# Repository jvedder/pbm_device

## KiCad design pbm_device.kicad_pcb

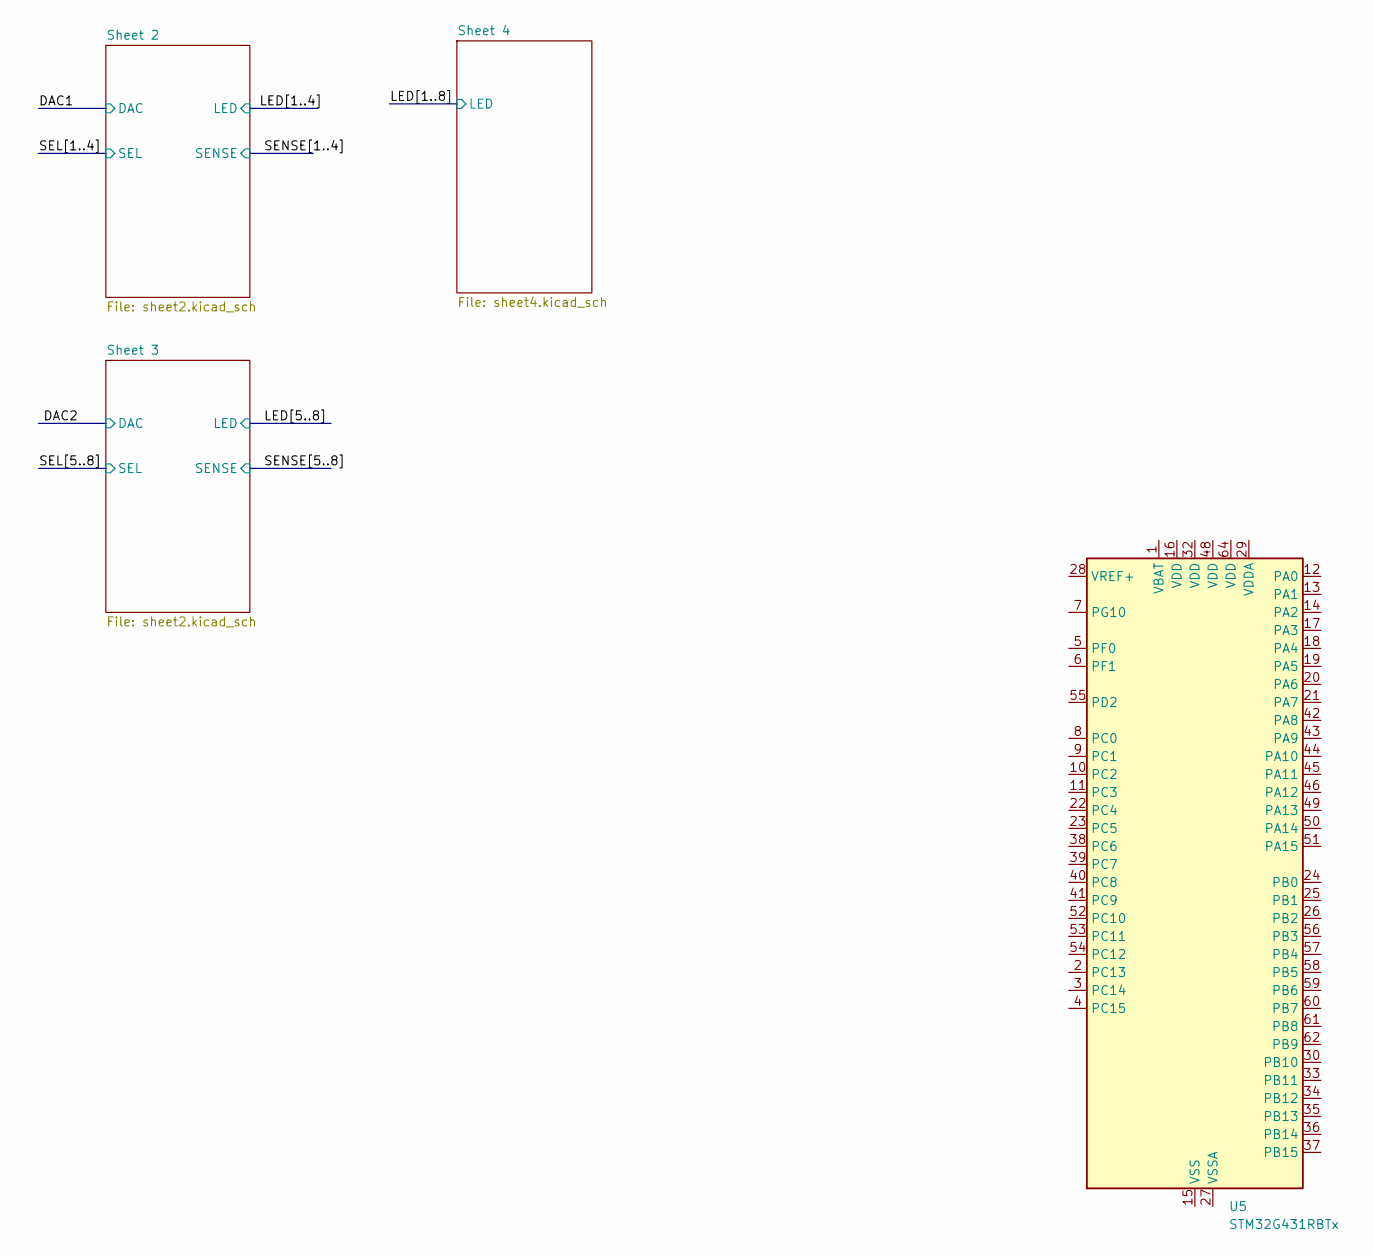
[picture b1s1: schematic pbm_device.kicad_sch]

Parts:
U5: STM32G431RBTx; LQFP-64_10x10mm_P0.5mm

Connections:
unnamed: U5.15 (VSS), U5.31 (VSS), U5.47 (VSS), U5.63 (VSS)

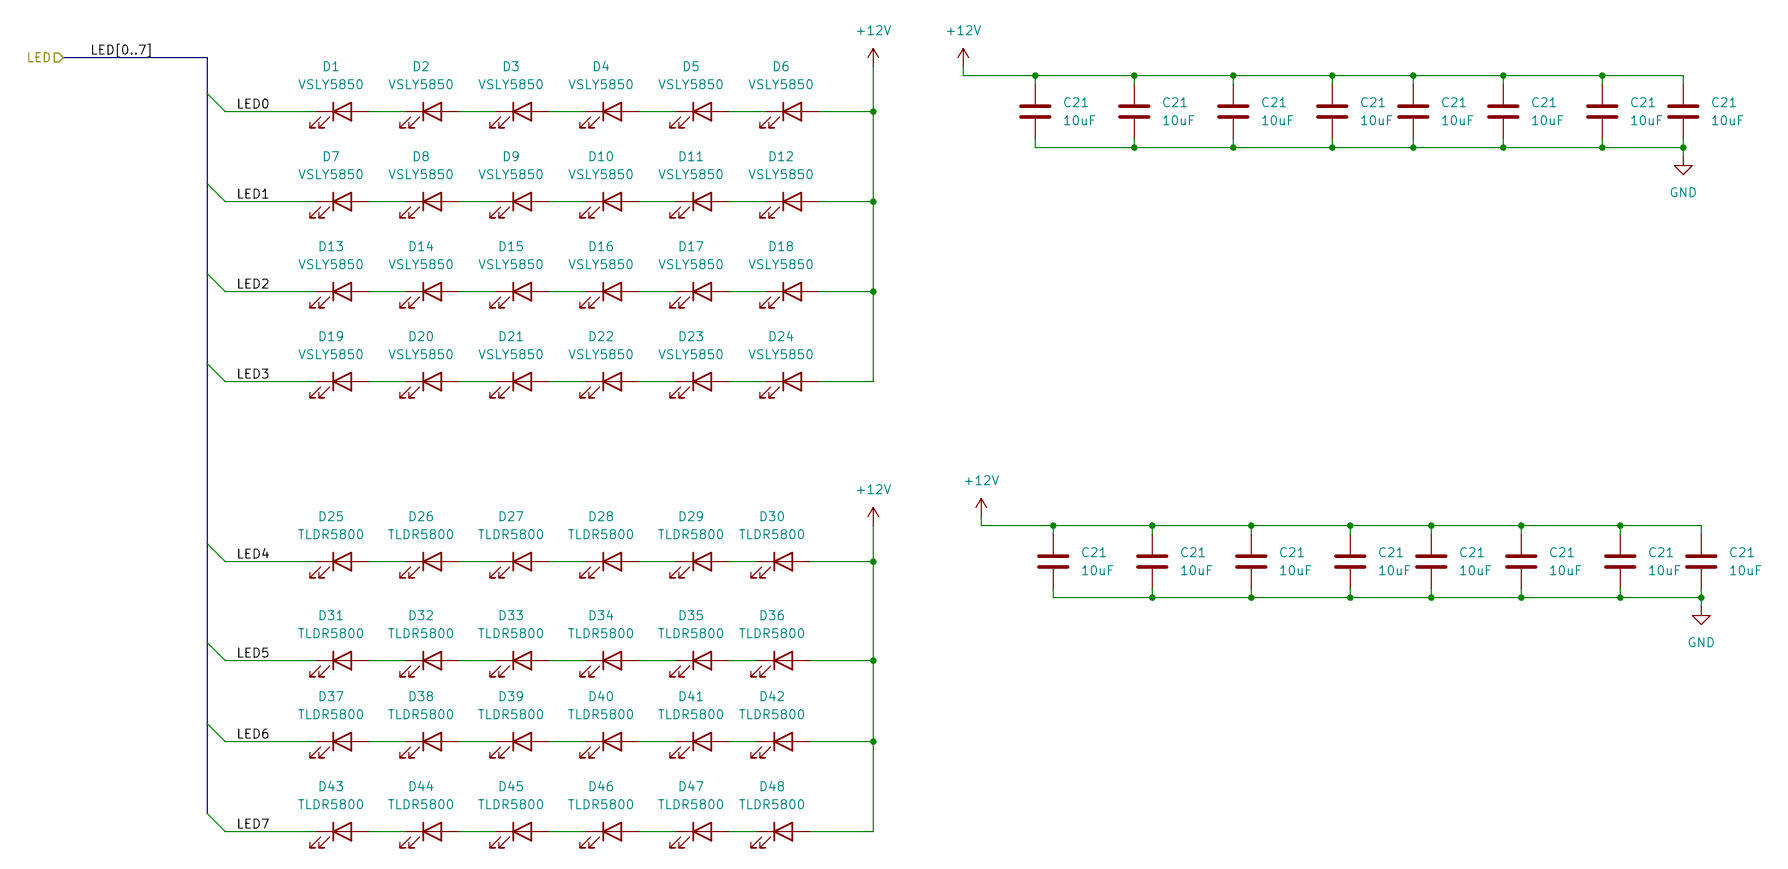
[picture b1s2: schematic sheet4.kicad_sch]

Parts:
C21: 10uF; R_0603_1608Metric_Pad0.98x0.95mm_HandSolder
D1, D2, D3, D4, D5, D6, D7, D8, D9, D10, D11, D12, D13, D14, D15, D16, D17, D18, D19, D20, D21, D22, D23, D24: VSLY5850; LED_D5.0mm
D25, D26, D27, D28, D29, D30, D31, D32, D33, D34, D35, D36, D37, D38, D39, D40, D41, D42, D43, D44, D45, D46, D47, D48: TLDR5800; LED_D5.0mm

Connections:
/LED1: D1.1 (K); also elsewhere on the board
/LED2: D7.1 (K); also elsewhere on the board
/LED3: D13.1 (K); also elsewhere on the board
/LED4: D19.1 (K); also elsewhere on the board
/LED5: D25.1 (K); also elsewhere on the board
/LED6: D31.1 (K); also elsewhere on the board
/LED7: D37.1 (K); also elsewhere on the board
/LED8: D43.1 (K); also elsewhere on the board
GND: C21.2; also elsewhere on the board
unnamed: D1.2 (A), D2.1 (K)
unnamed: D2.2 (A), D3.1 (K)
unnamed: D3.2 (A), D4.1 (K)
unnamed: D4.2 (A), D5.1 (K)
unnamed: D5.2 (A), D6.1 (K)
unnamed: D7.2 (A), D8.1 (K)
unnamed: D8.2 (A), D9.1 (K)
unnamed: D10.2 (A), D11.1 (K)
unnamed: D9.2 (A), D10.1 (K)
unnamed: D11.2 (A), D12.1 (K)
unnamed: D13.2 (A), D14.1 (K)
unnamed: D14.2 (A), D15.1 (K)
unnamed: D15.2 (A), D16.1 (K)
unnamed: D16.2 (A), D17.1 (K)
unnamed: D17.2 (A), D18.1 (K)
unnamed: D19.2 (A), D20.1 (K)
unnamed: D20.2 (A), D21.1 (K)
unnamed: D21.2 (A), D22.1 (K)
unnamed: D22.2 (A), D23.1 (K)
unnamed: D23.2 (A), D24.1 (K)
unnamed: D25.2 (A), D26.1 (K)
unnamed: D26.2 (A), D27.1 (K)
unnamed: D27.2 (A), D28.1 (K)
unnamed: D28.2 (A), D29.1 (K)
unnamed: D29.2 (A), D30.1 (K)
unnamed: D31.2 (A), D32.1 (K)
unnamed: D32.2 (A), D33.1 (K)
unnamed: D33.2 (A), D34.1 (K)
unnamed: D34.2 (A), D35.1 (K)
unnamed: D35.2 (A), D36.1 (K)
unnamed: D37.2 (A), D38.1 (K)
unnamed: D38.2 (A), D39.1 (K)
unnamed: D39.2 (A), D40.1 (K)
unnamed: D40.2 (A), D41.1 (K)
unnamed: D41.2 (A), D42.1 (K)
unnamed: D43.2 (A), D44.1 (K)
unnamed: D44.2 (A), D45.1 (K)
unnamed: D45.2 (A), D46.1 (K)
unnamed: D46.2 (A), D47.1 (K)
unnamed: D47.2 (A), D48.1 (K)

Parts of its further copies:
C5, C6, C7, C8, C9, C12, C13, C14, C15, C16, C17, C18, C19, C20, C22: 10uF; R_0603_1608Metric_Pad0.98x0.95mm_HandSolder

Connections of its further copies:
GND: C5.2, C6.2, C7.2, C8.2, C9.2, C12.2, C13.2, C14.2, C15.2, C16.2, C17.2, C18.2, C19.2, C20.2, C22.2; also elsewhere on the board

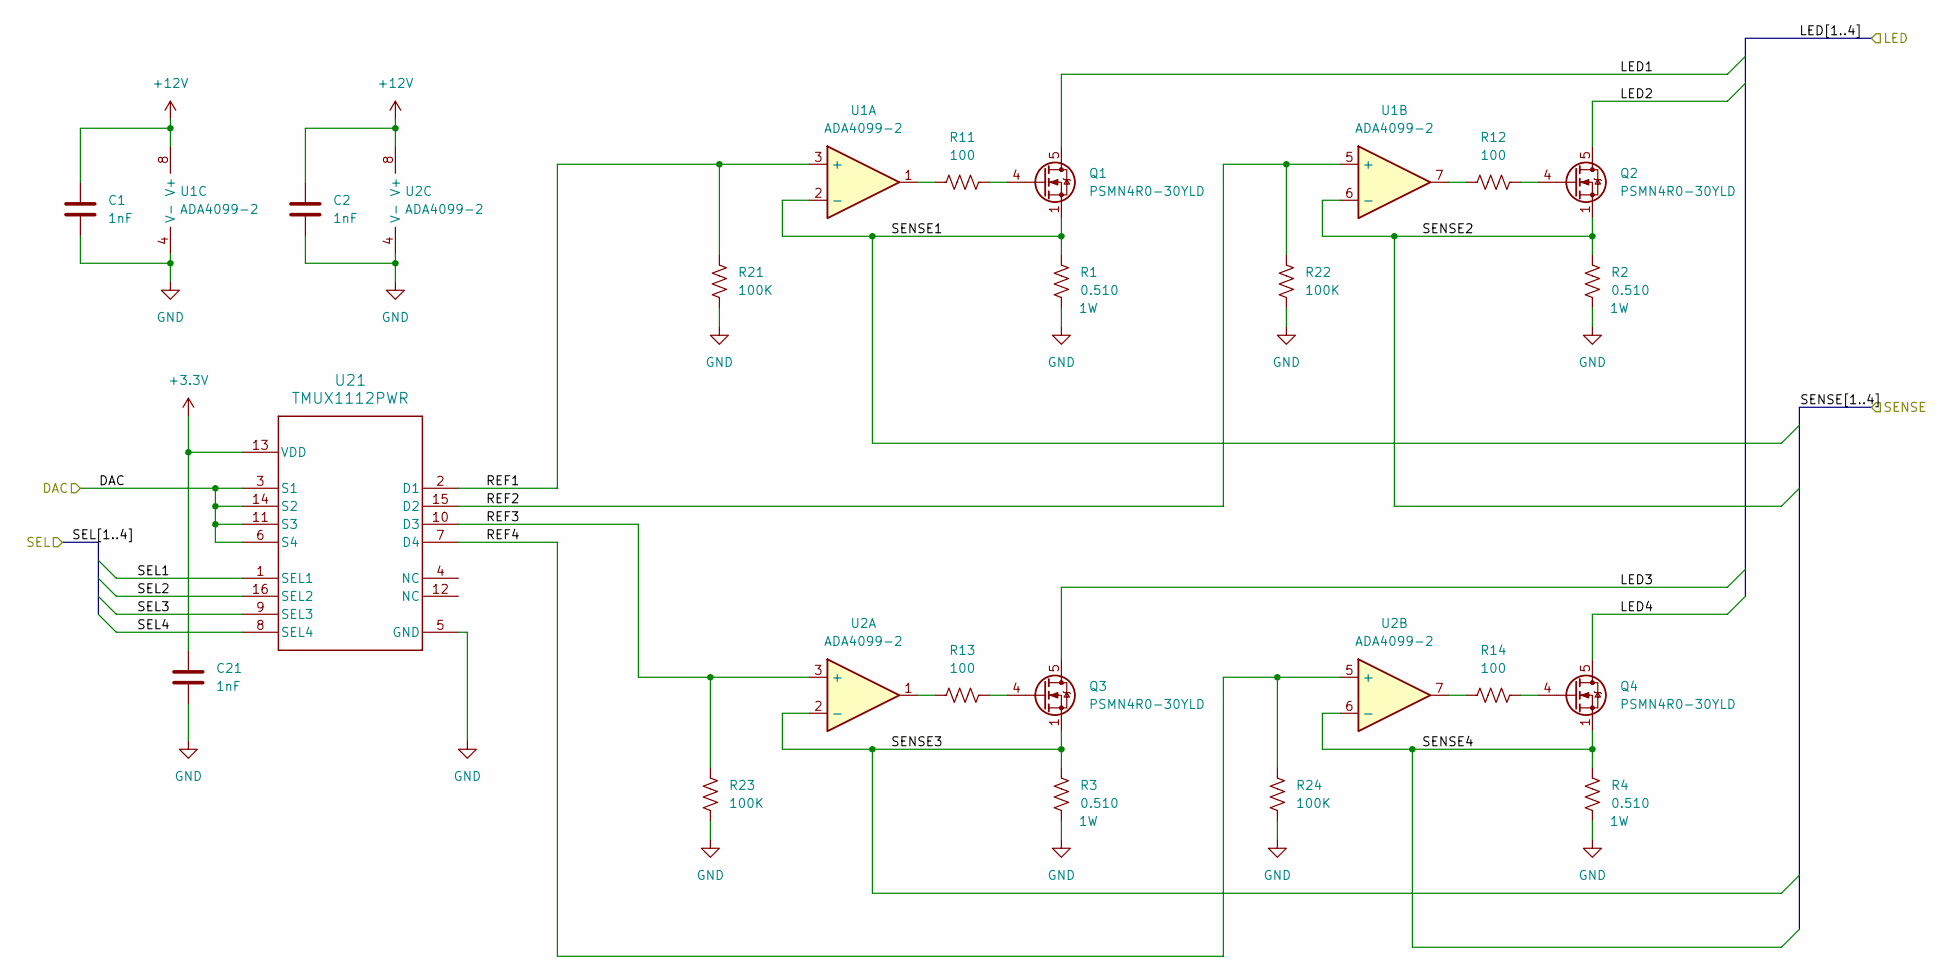
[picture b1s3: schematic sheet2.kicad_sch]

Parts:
C1, C2, C21: 1nF; R_0603_1608Metric_Pad0.98x0.95mm_HandSolder
Q1, Q2, Q3, Q4: PSMN4R0-30YLD; LFPAK56
R1, R2, R3, R4: 0.510; R_1210_3225Metric_Pad1.30x2.65mm_HandSolder; Mfg PN RCWE1210R510FKEA; Digikey RCWE.51FCT-ND
R11, R12, R13, R14: 100; R_0603_1608Metric_Pad0.98x0.95mm_HandSolder; Mfg PN CRCW0603100RFKEA; Digikey 541-100HCT-ND
R21, R22, R23, R24: 100K; R_0603_1608Metric_Pad0.98x0.95mm_HandSolder; Mfg PN CRCW0603100KFKEA; Digikey 541-100KHCT-ND
U1, U2: ADA4099-2; SOIC-8_3.9x4.9mm_P1.27mm; Mfg PN ADA4099-2BRZ; Digikey 505-ADA4099-2BRZ-ND
U21: TMUX1112PWR; PW0016A-IPC_A

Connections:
/LED1: Q1.5 (D); also elsewhere on the board
/LED2: Q2.5 (D); also elsewhere on the board
/LED3: Q3.5 (D); also elsewhere on the board
/LED4: Q4.5 (D); also elsewhere on the board
/SENSE1: Q1.1 (S), Q1.2 (S), Q1.3 (S), R1.1, U1.2 (-)
/SENSE2: Q2.1 (S), Q2.2 (S), Q2.3 (S), R2.1, U1.6 (-)
/SENSE3: Q3.1 (S), Q3.2 (S), Q3.3 (S), R3.1, U2.2 (-)
/SENSE4: Q4.1 (S), Q4.2 (S), Q4.3 (S), R4.1, U2.6 (-)
/Sheet 2/REF1: R21.1, U1.3 (+); also elsewhere on the board
/Sheet 2/REF2: R22.1, U1.5 (+); also elsewhere on the board
/Sheet 2/REF3: R23.1, U2.3 (+); also elsewhere on the board
/Sheet 2/REF4: R24.1, U2.5 (+); also elsewhere on the board
GND: C1.2, C2.2, C21.2, R1.2, R2.2, R3.2, R4.2, R21.2, R22.2, R23.2, R24.2, U1.4 (V-), U2.4 (V-); also elsewhere on the board
unnamed: Q1.4 (G), R11.2
unnamed: Q2.4 (G), R12.2
unnamed: Q3.4 (G), R13.2
unnamed: Q4.4 (G), R14.2
unnamed: R11.1, U1.1
unnamed: R12.1, U1.7
unnamed: R13.1, U2.1
unnamed: R14.1, U2.7

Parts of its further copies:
C3, C4, C10, C11: 1nF; R_0603_1608Metric_Pad0.98x0.95mm_HandSolder
Q5, Q6, Q7, Q8: PSMN4R0-30YLD; LFPAK56
R5, R6, R7, R8: 0.510; R_1210_3225Metric_Pad1.30x2.65mm_HandSolder; Mfg PN RCWE1210R510FKEA; Digikey RCWE.51FCT-ND
R15, R16, R17, R18: 100; R_0603_1608Metric_Pad0.98x0.95mm_HandSolder; Mfg PN CRCW0603100RFKEA; Digikey 541-100HCT-ND
R25, R26, R27, R28: 100K; R_0603_1608Metric_Pad0.98x0.95mm_HandSolder; Mfg PN CRCW0603100KFKEA; Digikey 541-100KHCT-ND
U3, U4: ADA4099-2; SOIC-8_3.9x4.9mm_P1.27mm; Mfg PN ADA4099-2BRZ; Digikey 505-ADA4099-2BRZ-ND
U10, U11: TMUX1112PWR; PW0016A-IPC_A

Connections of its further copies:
/DAC1: U10.3 (S1), U10.6 (S4), U10.11 (S3), U10.14 (S2)
/DAC2: U11.3 (S1), U11.6 (S4), U11.11 (S3), U11.14 (S2)
/LED5: Q5.5 (D); also elsewhere on the board
/LED6: Q6.5 (D); also elsewhere on the board
/LED7: Q7.5 (D); also elsewhere on the board
/LED8: Q8.5 (D); also elsewhere on the board
/SEL1: U10.1 (SEL1)
/SEL2: U10.16 (SEL2)
/SEL3: U10.9 (SEL3)
/SEL4: U10.8 (SEL4)
/SEL5: U11.1 (SEL1)
/SEL6: U11.16 (SEL2)
/SEL7: U11.9 (SEL3)
/SEL8: U11.8 (SEL4)
/SENSE5: Q5.1 (S), Q5.2 (S), Q5.3 (S), R5.1, U3.2 (-)
/SENSE6: Q6.1 (S), Q6.2 (S), Q6.3 (S), R6.1, U3.6 (-)
/SENSE7: Q7.1 (S), Q7.2 (S), Q7.3 (S), R7.1, U4.2 (-)
/SENSE8: Q8.1 (S), Q8.2 (S), Q8.3 (S), R8.1, U4.6 (-)
/Sheet 2/REF1: U10.2 (D1); also elsewhere on the board
/Sheet 2/REF2: U10.15 (D2); also elsewhere on the board
/Sheet 2/REF3: U10.10 (D3); also elsewhere on the board
/Sheet 2/REF4: U10.7 (D4); also elsewhere on the board
/Sheet 3/REF1: R25.1, U3.3 (+), U11.2 (D1)
/Sheet 3/REF2: R26.1, U3.5 (+), U11.15 (D2)
/Sheet 3/REF3: R27.1, U4.3 (+), U11.10 (D3)
/Sheet 3/REF4: R28.1, U4.5 (+), U11.7 (D4)
GND: C3.2, C4.2, C10.2, C11.2, R5.2, R6.2, R7.2, R8.2, R25.2, R26.2, R27.2, R28.2, U3.4 (V-), U4.4 (V-), U10.5 (GND), U11.5 (GND); also elsewhere on the board
unnamed: Q5.4 (G), R15.2
unnamed: Q6.4 (G), R16.2
unnamed: Q7.4 (G), R17.2
unnamed: Q8.4 (G), R18.2
unnamed: R15.1, U3.1
unnamed: R16.1, U3.7
unnamed: R17.1, U4.1
unnamed: R18.1, U4.7

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
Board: 2 copper layers, 109 parts (0 on the bottom side), 86 nets, no tracks yet.

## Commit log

2024-01-13 Initial Commit. Started LED placement
